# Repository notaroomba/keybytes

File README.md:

<h1 align="center">
  <br>
  
  <br>
</h1>

<h4 align="center">
A truly modular keyboard with rearrangeable keys, magnetic cases and Bluetooth!
</h4>

<div align="center">

</div>

<p align="center">
  <a href="#key-features">Key Features</a> •
  <a href="#video-demo">Video Demo</a> •
  <a href="#connecting-keybits">Connecting Keybits</a> •
  <a href="#pcb">PCB</a> •
  <a href="#credits">Credits</a> •
  <a href="#license">License</a>
</p>

<p align="center">
  
  <br>
  <i>(v2 preview)</i>
</p>

## Video Demo

https://github.com/user-attachments/assets/19bec26d-6e01-4ee0-906e-7e69bace2f9c

Typing over USB:

https://github.com/user-attachments/assets/b6abd347-b68b-40f1-8e2d-c50744b8104e

## Key Features

- **Rearrangeable layout** where every key is its own 1u PCB
- **CH592F** RISC-V microcontroller with BLE and USB on every key
- **Cross shaped 2 layer flex PCB** that folds up into the case, with FR4 stiffeners
- **Magnet contacts** on all 4 sides, 6 per side (1x2mm N52) on a 2.38mm grid
- **Any rotation** and 0/25/50/75% stagger between keys
- **Polarity independent** sides, a small FET bridge on each side sorts out VBUS and GND
- **WS2812 RGB LED** on every key
- **Mill-Max 3305** hot swap sockets
- **Hall variant** with a TMAG3001 3-axis hall sensor, so the same board can be a hall key, a knob or a joystick
- **Keyword** main board with a CH592F, BLE and USB-C
- **Battery charging** with the BQ25185 for a small LiPo
- **USB-C** with ESD protection (USBLC6)
- **Pogo pin flashing** of every Keybit from the Keyword, then OTA updates
- **Flex spacers** (1u, 0.75u and 0.5u) to pass power across gaps

## V1

V1 had a CH32V003 on every key with pogo pins on all 4 sides and an STM32WB55 Keyword split into two stacked PCBs. It lives in the [`v1`](https://github.com/notaroomba/keybytes/tree/v1) branch.

## Connecting Keybits

The side contacts are the magnets themselves. Every side has 6 contact magnets on a 2.38mm grid with the A and B nets alternating, so two keybits connect no matter which way round they are and at any 0/25/50/75% stagger. Each side has a small FET bridge that connects whichever net is higher to VBUS and the other one to GND, so polarity doesn't matter either.

**Flashing keybits:** the 4 pogo pins on top of the keyword (GND, TIO, TCK, 3V3) line up with the pads on the bottom of every keybit, so a keybit gets flashed by pressing it onto the keyword. After that it updates over OTA.

The v2 firmware for the CH592F is still in progress. The v1 status LED codes are in the [`v1`](https://github.com/notaroomba/keybytes/tree/v1) branch.

## PCB

Designed in KiCad! There are two main boards, the Keybit and the Keyword, plus passive flex spacers (1u, 0.75u and 0.5u) that pass power across gaps.

### Keybit

A single key on a cross shaped 2 layer flex PCB with a CH592F in the middle, a WS2812 RGB LED and Mill-Max 3305 hot swap sockets for the switch. The 4 flaps fold up into the case and have FR4 stiffeners, and each one has 6 contact magnets and a FET bridge for power. The pads on the bottom are for flashing it from the keyword. The hall variant has a TMAG3001 3-axis hall sensor, so the same board can be a hall key, a knob (in the encoder case) or a joystick.

**Schematic:**

**Layout:**

**3D View:**

### Keyword

The main board that the keybits connect to. It is now one flex board with a CH592F for BLE and USB-C, a BQ25185 charger for a small LiPo and a USBLC6 for ESD protection. The 4 SMD pogo pins on the top (GND, TIO, TCK, 3V3) are for flashing the keybits.

**Schematic:**

**Layout:**

**3D View:**

### Manufacturing

Everything is panelized for JLC flex PCBA. The files are in [`production/panels`](production/panels): `8x3-panel` is the full order, `2x3-test-panel` is a smaller test order and `spacer-panel` is the bare flex spacers.

## Credits

This project uses:

- [KiCad](https://www.kicad.org/)
- [OnShape](https://www.onshape.com/) for case design
- [Blender](https://www.blender.org/) for 3D renders
- [ch32fun](https://github.com/cnlohr/ch32fun) and the WCH SDK for the CH592F
- [Formlabs](https://formlabs.com/) for resin printing
- [Hack Club Forge](https://forge.hackclub.com/)
- [JLCPCB](https://jlcpcb.com/) for PCB fabrication and assembly
- [JLCCNC](https://jlccnc.com/) for the encoder knob

## You may also like...

- [Ember](https://github.com/NotARoomba/ember) - A USB-C powered reflow hotplate with Bluetooth
- [Cyberboard](https://github.com/NotARoomba/Cyberboard) - A Raspberry Pi Pico-sized STM32 development board with Bluetooth
- [Trace](https://github.com/NotARoomba/Trace) - A comprehensive PCB ruler with reference footprints
- [Linea](https://github.com/NotARoomba/Linea) - An EMR tablet

## License

MIT

---

> [notaroomba.dev](https://notaroomba.dev) &nbsp;&middot;&nbsp;
> GitHub [@NotARoomba](https://github.com/NotARoomba) &nbsp;&middot;&nbsp;

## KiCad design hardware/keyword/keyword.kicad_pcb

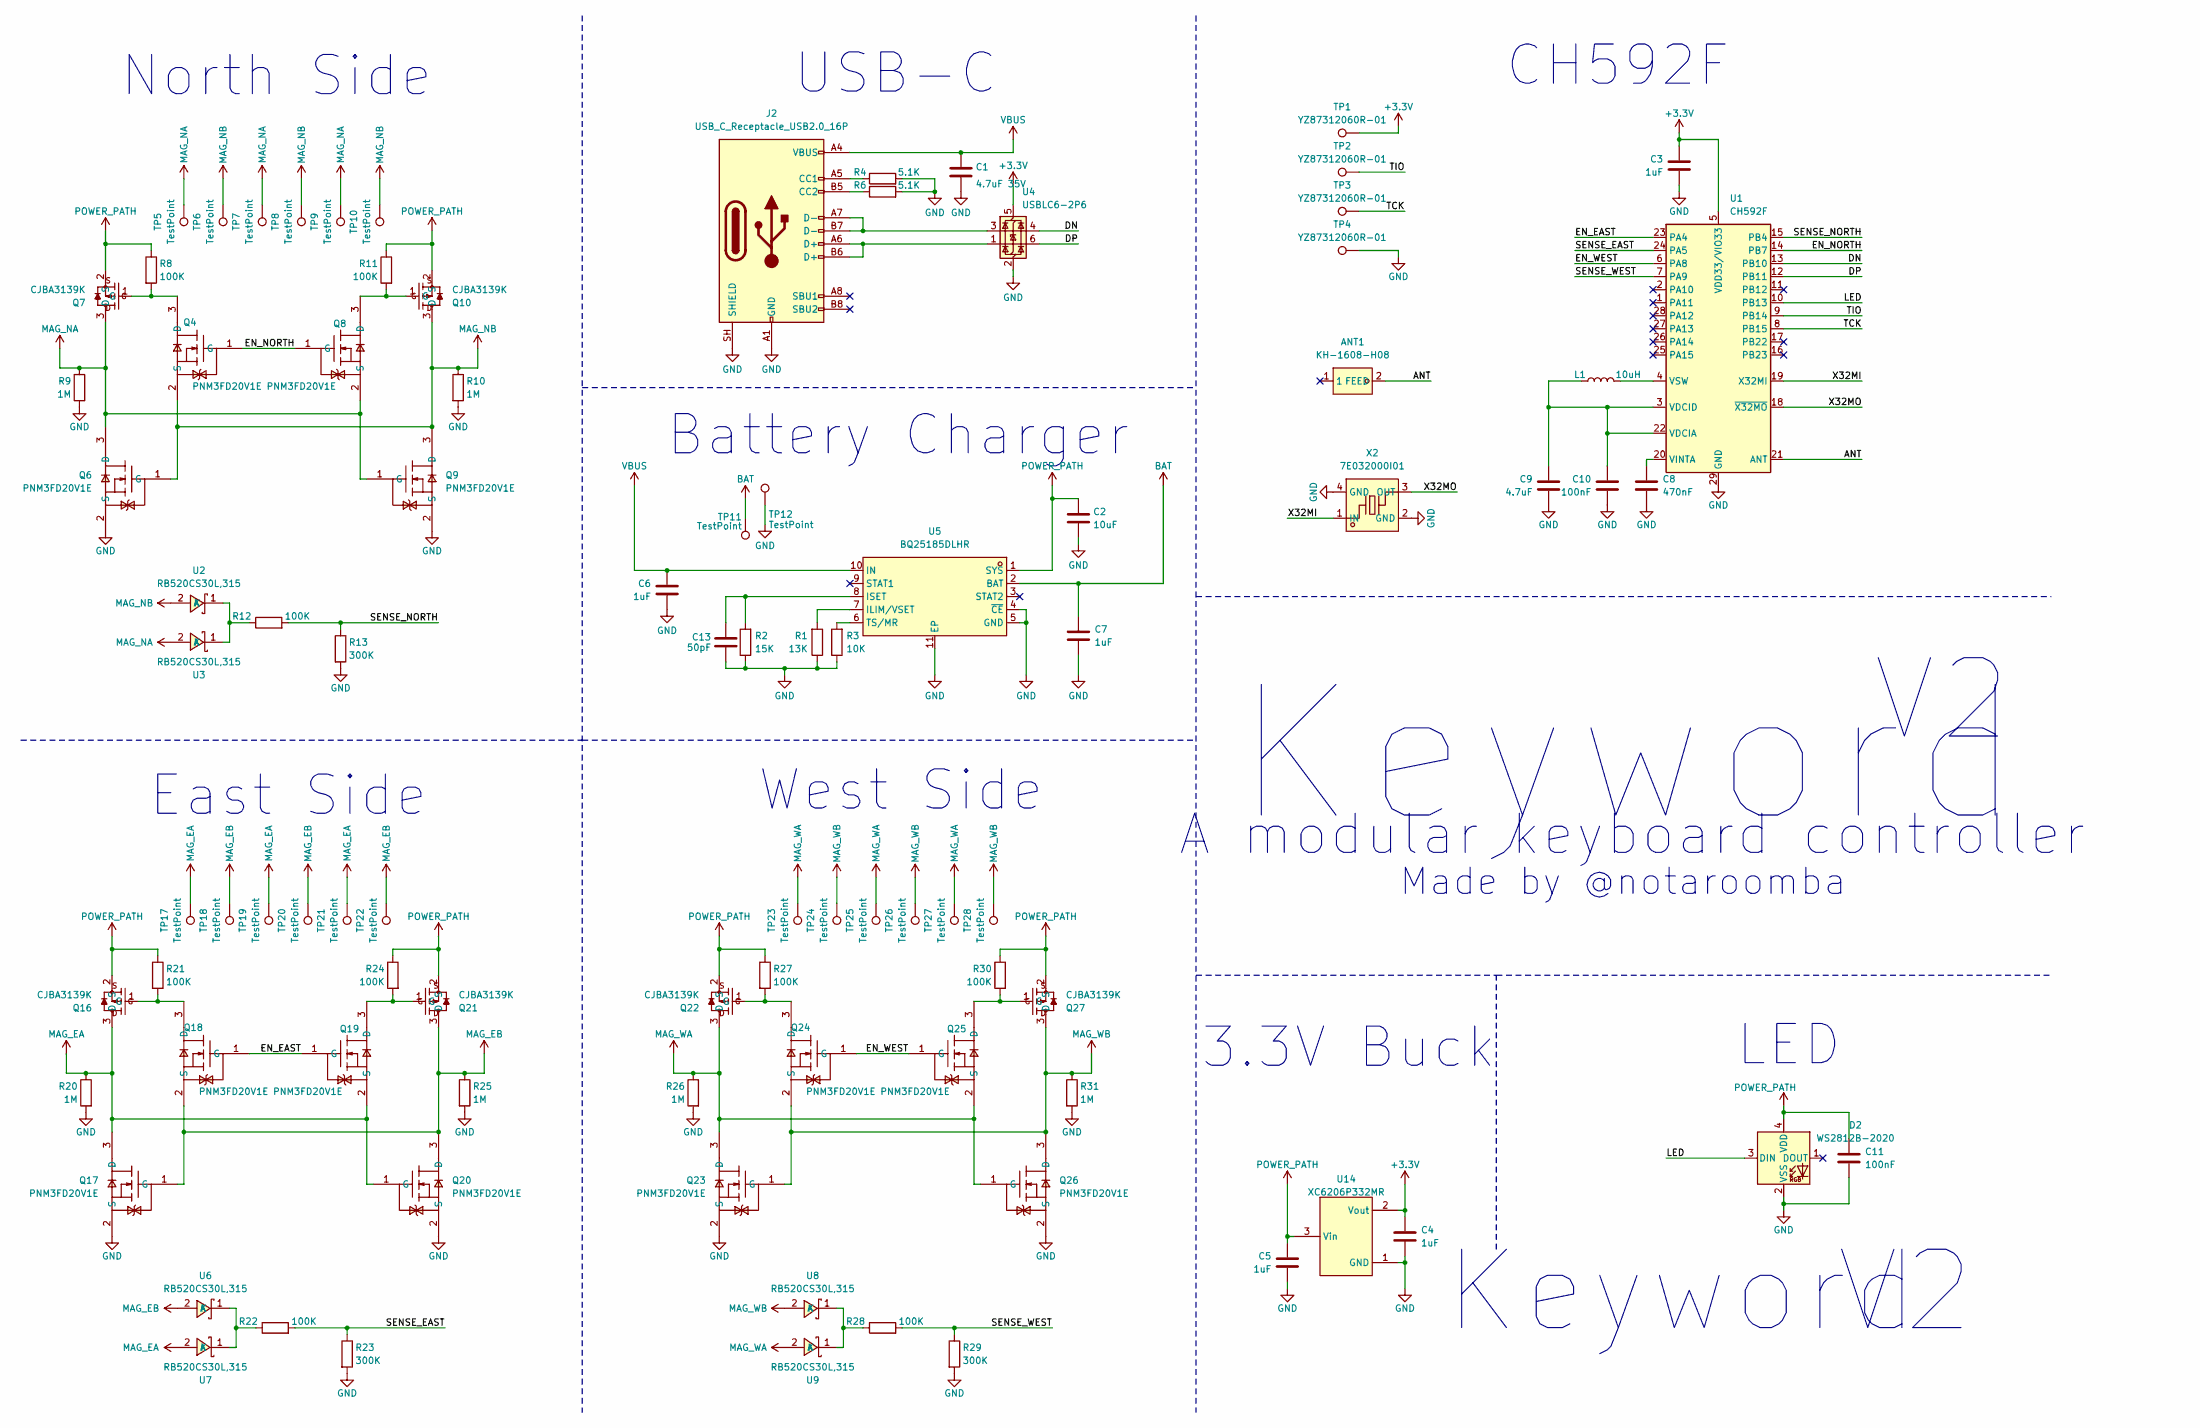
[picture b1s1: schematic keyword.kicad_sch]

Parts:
ANT1: KH-1608-H08; ANT-SMD_L1.7-W0.9; MPN KH-1608-H08; LCSC Part C2925416
C1: 4.7uF 35V; C_0603_1608Metric; LCSC C307467
C2: 10uF; C_0402_1005Metric; LCSC Part C6119763
C3, C4, C5, C6, C7: 1uF; C_0402_1005Metric; MPN CL05A105KA5NQNC; LCSC Part C52923
C8: 470nF; C_0402_1005Metric; MPN CL05A474KP5NNNC; LCSC Part C47339
C9: 4.7uF; C_0402_1005Metric; MPN CL05A475MP5NRNC; LCSC Part C23733
C10, C11: 100nF; C_0402_1005Metric; MPN CL05B104KO5NNNC; LCSC Part C1525
C13: 50pF; C_0402_1005Metric; LCSC Part C49210433
D2: WS2812B-2020; LED_WS2812B-2020_PLCC4_2.0x2.0mm; MPN WS2812B-2020-V6; LCSC Part C52917434
J2: USB_C_Receptacle_USB2.0_16P; USB_C_Receptacle_HCTL_HC-TYPE-C-16P-01A; LCSC C2894897
L1: 10uH; L_0402_1005Metric; MPN MWI0402IF100KST-HF; LCSC Part C48946156
Q4, Q6, Q8, Q9, Q17, Q18, Q19, Q20, Q23, Q24, Q25, Q26: PNM3FD20V1E; SOT-883-3_L1.0-W0.6-BR; MPN PNM3FD20V1E; LCSC Part C2875806
Q7, Q10, Q16, Q21, Q22, Q27: CJBA3139K; DFN1006-3L_L1.0-W0.6-LS1.0-BR; MPN CJBA3139K; LCSC Part C504099
R1: 13K; R_0402_1005Metric; LCSC Part C49653083
R2: 15K; R_0402_1005Metric; LCSC Part C25756
R3: 10K; R_0402_1005Metric; LCSC Part C25744
R4, R6: 5.1K; R_0402_1005Metric; LCSC Part C25905
R8, R11, R12, R21, R22, R24, R27, R28, R30: 100K; R_0402_1005Metric; MPN 0402WGF1003TCE; LCSC Part C25741
R9, R10, R20, R25, R26, R31: 1M; R_0402_1005Metric; MPN 0402WGF1004TCE; LCSC Part C26083
R13, R23, R29: 300K; R_0402_1005Metric; MPN 0402WGF3003TCE; LCSC Part C25774
TP1, TP2, TP3, TP4: YZ87312060R-01; POGO-SMD_YZ87312060R-01; LCSC Part C5157406
TP5, TP6, TP7, TP8, TP9, TP10, TP17, TP18, TP19, TP20, TP21, TP22, TP23, TP24, TP25, TP26, TP27, TP28: TestPoint; TestPoint_Pad_D1.0mm
TP11, TP12: TestPoint; TestPoint_Pad_1.0x1.0mm
U1: CH592F; WQFN-28-1EP_4x4mm_P0.4mm_EP2.7x2.7mm; MPN CH592F; LCSC Part C39831287
U2, U3, U6, U7, U8, U9: RB520CS30L,315; X1-DFN1006-2_L1.0-W0.6-RD; MPN RB520CS30L,315; LCSC Part C461213
U4: USBLC6-2P6; SOT-666; LCSC Part C53059594
U5: BQ25185DLHR; WSON-10_L2.2-W2.0-P0.40-BL-EP_TI_DLH0010A; MPN BQ25185DLHR; LCSC Part C19725033
U14: XC6206P332MR; SOT-23-3_L2.9-W1.6-P1.90-LS2.8-BR; MPN XC6206P332MR-G; LCSC Part C5446
X2: 7E032000I01; CRYSTAL-SMD_4P-L1.6-W1.2-BL; MPN 7E032000I01; LCSC Part C781732

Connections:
+3.3V: C3.1, C4.1, TP1.1 (1_1), U1.5 (VDD33/VIO33), U4.5 (VBUS), U14.2 (Vout)
/ANT: ANT1.2 (FEED_2), U1.21 (ANT)
/DN: U1.13 (PB10), U4.4 (I/O2)
/DP: U1.12 (PB11), U4.6 (I/O1)
/EN_EAST: Q18.1 (G), Q19.1 (G), U1.23 (PA4)
/EN_NORTH: Q4.1 (G), Q8.1 (G), U1.14 (PB7)
/EN_WEST: Q24.1 (G), Q25.1 (G), U1.6 (PA8)
/LED: D2.3 (DIN), U1.10 (PB13)
/SENSE_EAST: R22.2, R23.1, U1.24 (PA5)
/SENSE_NORTH: R12.2, R13.1, U1.15 (PB4)
/SENSE_WEST: R28.2, R29.1, U1.7 (PA9)
/TCK: TP3.1 (1_1), U1.8 (PB15)
/TIO: TP2.1 (1_1), U1.9 (PB14)
/X32MI: U1.19 (X32MI), X2.1 (IN)
/X32MO: U1.18 (~X32MO), X2.3 (OUT)
BAT: C7.1, TP11.1 (1_1), U5.2 (BAT)
GND: C1.2, C2.2, C3.2, C4.2, C5.2, C6.2, C7.2, C8.2, C9.2, C10.2, C11.2, C13.2, D2.2 (VSS), J2.A1 (GND), J2.A12 (GND), J2.B1 (GND), J2.B12 (GND), J2.SH (SHIELD), Q6.2 (S), Q9.2 (S), Q17.2 (S), Q20.2 (S), Q23.2 (S), Q26.2 (S), R1.1, R2.1, R3.1, R4.2, R6.2, R9.2, R10.2, R13.2, R20.2, R23.2, R25.2, R26.2, R29.2, R31.2, TP4.1 (1_1), TP12.1 (1_1), U1.29 (GND), U4.2 (GND), U5.4 (~CE), U5.5 (GND), U5.11 (EP), U14.1 (GND), X2.2 (GND), X2.4 (GND)
MAG_EA: Q16.3 (D), Q17.3 (D), Q19.2 (S), Q20.1 (G), R20.1, TP17.1 (1_1), TP19.1 (1_1), TP21.1 (1_1), U7.2 (A)
MAG_EB: Q17.1 (G), Q18.2 (S), Q20.3 (D), Q21.3 (D), R25.1, TP18.1 (1_1), TP20.1 (1_1), TP22.1 (1_1), U6.2 (A)
MAG_NA: Q6.3 (D), Q7.3 (D), Q8.2 (S), Q9.1 (G), R9.1, TP5.1 (1_1), TP7.1 (1_1), TP9.1 (1_1), U3.2 (A)
MAG_NB: Q4.2 (S), Q6.1 (G), Q9.3 (D), Q10.3 (D), R10.1, TP6.1 (1_1), TP8.1 (1_1), TP10.1 (1_1), U2.2 (A)
MAG_WA: Q22.3 (D), Q23.3 (D), Q25.2 (S), Q26.1 (G), R26.1, TP23.1 (1_1), TP25.1 (1_1), TP27.1 (1_1), U9.2 (A)
MAG_WB: Q23.1 (G), Q24.2 (S), Q26.3 (D), Q27.3 (D), R31.1, TP24.1 (1_1), TP26.1 (1_1), TP28.1 (1_1), U8.2 (A)
unnamed: J2.A5 (CC1), R4.1
unnamed: J2.B5 (CC2), R6.1
unnamed: J2.A6 (D+), J2.B6 (D+), U4.1 (I/O1)
unnamed: J2.A7 (D-), J2.B7 (D-), U4.3 (I/O2)
unnamed: Q4.3 (D), Q7.1 (G), R8.2
unnamed: Q8.3 (D), Q10.1 (G), R11.2
unnamed: Q16.1 (G), Q18.3 (D), R21.2
unnamed: Q19.3 (D), Q21.1 (G), R24.2
unnamed: Q22.1 (G), Q24.3 (D), R27.2
unnamed: Q25.3 (D), Q27.1 (G), R30.2
unnamed: C9.1, C10.1, L1.1, U1.3 (VDCID), U1.22 (VDCIA)
unnamed: C8.1, U1.20 (VINTA)
unnamed: L1.2, U1.4 (VSW)
unnamed: R12.1, U2.1 (K), U3.1 (K)
unnamed: R1.2, U5.7 (ILIM/VSET)
unnamed: C13.1, R2.2, U5.8 (ISET)
unnamed: R3.2, U5.6 (TS/MR)
unnamed: R22.1, U6.1 (K), U7.1 (K)
unnamed: R28.1, U8.1 (K), U9.1 (K)
POWER_PATH: C2.1, C5.1, C11.1, D2.4 (VDD), Q7.2 (S), Q10.2 (S), Q16.2 (S), Q21.2 (S), Q22.2 (S), Q27.2 (S), R8.1, R11.1, R21.1, R24.1, R27.1, R30.1, U5.1 (SYS), U14.3 (Vin)
VBUS: C1.1, C6.1, J2.A4 (VBUS), J2.A9 (VBUS), J2.B4 (VBUS), J2.B9 (VBUS), U5.10 (IN)

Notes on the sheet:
CH592F
West Side
North Side
Battery Charger
LED
Made by @notaroomba
3.3V Buck
East Side
Keyword
A modular keyboard controller
USB-C

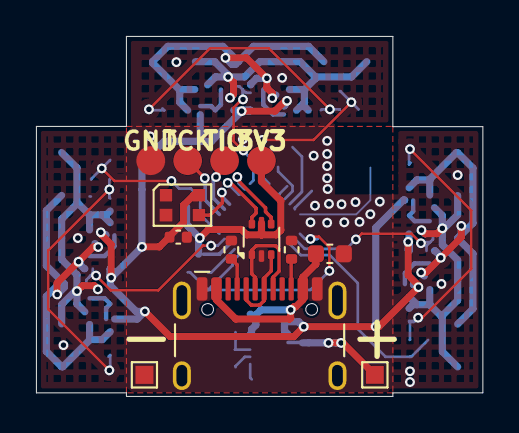
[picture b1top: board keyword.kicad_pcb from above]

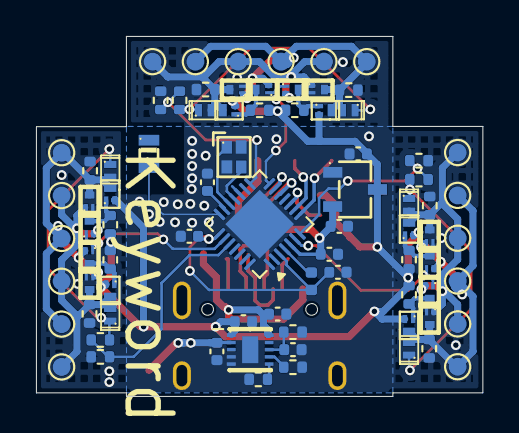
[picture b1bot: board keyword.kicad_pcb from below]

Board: 2 copper layers, 24.8 x 20.0 mm, 92 parts (79 on the bottom side), 44 nets.

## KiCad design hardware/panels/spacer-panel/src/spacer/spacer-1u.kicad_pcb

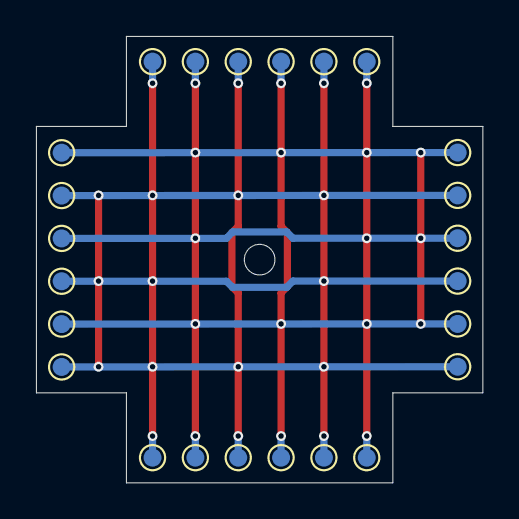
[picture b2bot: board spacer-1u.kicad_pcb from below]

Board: 2 copper layers, 24.8 x 24.8 mm, 24 parts (24 on the bottom side), 2 nets.

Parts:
TP5, TP6, TP7, TP8, TP9, TP10, TP11, TP12, TP13, TP14, TP15, TP16, TP17, TP18, TP19, TP20, TP21, TP22, TP23, TP24, TP25, TP26, TP27, TP28: TestPoint; TestPoint_Pad_D1.0mm

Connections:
SPX: TP5.1 (1_1), TP7.1 (1_1), TP9.1 (1_1), TP12.1 (1_1), TP14.1 (1_1), TP16.1 (1_1), TP17.1 (1_1), TP19.1 (1_1), TP21.1 (1_1), TP24.1 (1_1), TP26.1 (1_1), TP28.1 (1_1)
SPY: TP6.1 (1_1), TP8.1 (1_1), TP10.1 (1_1), TP11.1 (1_1), TP13.1 (1_1), TP15.1 (1_1), TP18.1 (1_1), TP20.1 (1_1), TP22.1 (1_1), TP23.1 (1_1), TP25.1 (1_1), TP27.1 (1_1)

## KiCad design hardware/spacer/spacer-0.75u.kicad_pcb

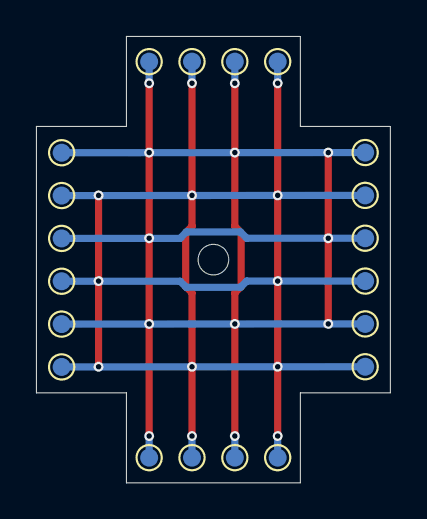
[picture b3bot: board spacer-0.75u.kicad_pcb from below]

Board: 2 copper layers, 19.7 x 24.8 mm, 20 parts (20 on the bottom side), 2 nets.

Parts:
TP5, TP7, TP8, TP10, TP11, TP13, TP14, TP16, TP17, TP18, TP19, TP20, TP21, TP22, TP23, TP24, TP25, TP26, TP27, TP28: TestPoint; TestPoint_Pad_D1.0mm

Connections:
SPX: TP5.1 (1_1), TP7.1 (1_1), TP14.1 (1_1), TP16.1 (1_1), TP17.1 (1_1), TP19.1 (1_1), TP21.1 (1_1), TP24.1 (1_1), TP26.1 (1_1), TP28.1 (1_1)
SPY: TP8.1 (1_1), TP10.1 (1_1), TP11.1 (1_1), TP13.1 (1_1), TP18.1 (1_1), TP20.1 (1_1), TP22.1 (1_1), TP23.1 (1_1), TP25.1 (1_1), TP27.1 (1_1)

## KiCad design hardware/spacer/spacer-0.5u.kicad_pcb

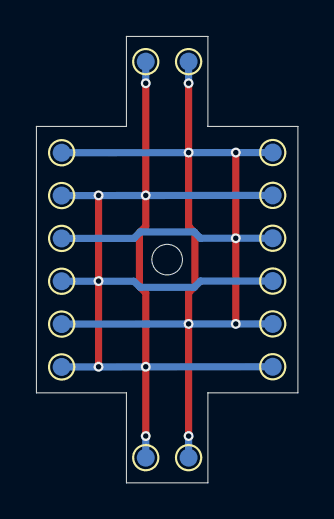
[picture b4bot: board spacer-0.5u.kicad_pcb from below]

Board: 2 copper layers, 14.5 x 24.8 mm, 16 parts (16 on the bottom side), 2 nets.

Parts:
TP5, TP10, TP11, TP16, TP17, TP18, TP19, TP20, TP21, TP22, TP23, TP24, TP25, TP26, TP27, TP28: TestPoint; TestPoint_Pad_D1.0mm

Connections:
SPX: TP5.1 (1_1), TP16.1 (1_1), TP17.1 (1_1), TP19.1 (1_1), TP21.1 (1_1), TP24.1 (1_1), TP26.1 (1_1), TP28.1 (1_1)
SPY: TP10.1 (1_1), TP11.1 (1_1), TP18.1 (1_1), TP20.1 (1_1), TP22.1 (1_1), TP23.1 (1_1), TP25.1 (1_1), TP27.1 (1_1)

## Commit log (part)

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2025-12-19 keybites test
2026-03-29 before flip
2026-04-04 add in stuff
2026-04-06 finished
2026-04-07 undo corners
2026-04-08 finish case and stuff
2026-04-10 add in mousebites
2026-04-10 stuff
2026-06-03 blender and stuff
2026-06-18 aaaaaaaaa
2026-06-20 renders
2026-06-20 Add .gitignore for .claude local settings
2026-06-29 aaaa
